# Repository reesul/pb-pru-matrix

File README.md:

# Pocket Beagle Audio Visualizer with LED matrix

Audio visualization is neat so I made a gadget with PocketBeagle for the hell of it! 

[See longer video below](./README.md#video-of-the-thing)

## Project Summary

I made a PCB ("cape" in Beagle terminology) that has an audio jack + electret mic to capture and amplify audio, plus the output cabling for a [LED panel from Adafruit](https://www.adafruit.com/product/2278) (but my extras were cheapo Aliexpress/where-ever and work identically). 

The PocketBeagle (PB) has an AM335x processor for the processing. I capture audio with ADC input in chunks with a sliding window -- sampling rate was set based on processing speed (unoptimized w/ numpy calls) and responsiveness. Audio is processed with FFT -> power log spectrum -> log-frequency power spectrum to make the basis for the image. The image is then an opencv color mapping for each (pseudo-log) frequency bin's power, and send to the PRU via /dev/mem so it can be displayed to the 64x32 LED matrix. The PRU is running a driver to display 8-bit color images, FPS somewhere in 20-30 range.

I chose a pocket beagle, partly because I've worked as an Apps Engineer at TI, partly b I have met the awesome Beagle folks several times, and partly bc I wanted to try running on an SoC with fast IO core + reasonable A-core running Linux. It's worked out well, and the examples were definitely present enough out there to get me started on all aspects of the project. That said, it helps a lot to have worked professionally with such devices to heterogeneous SoCs running a mixture of HLOS/RTOS/No-OS (esp. including Linux) and have a signal processing / embedded systems background. 

## V1 Details

First version of this project is complete as of 2024 EoY. I started sometime in 2023, but didn't put much time into it / slowed down by silly roadblocks. 

This v1 includes:
* Custom cape (PCB that beagle board attaches to) that provides audio input and image output signalling to the matrix panel
   * Revisions needed to reduce analog noise, reduce pinout/external connection, etc.
* PRU code that reads an image from shared memory, and manages output pins for the matrix such that we visualize an 8-bit, 32x64 pixel image. 
   * Framerate is 20-30 FPS and looks about reasonably smooth and responsive, albeit a bit jittery
* Updated device tree overlay for setting ADC configuartion (20kS/s) (see [dtb](./dtb/) files)
   * Data arrives through IIO driver and read with sysfs
   * I noted that bb-overlay repo (origin of these DTS) has an ./install.sh that doesn't work. I had to look in /boot/uEnv.txt to apply the DTBO file (name_overlays)
   * Sampling rate was chosen based on processing speed vs. responsiveness. I wanted 40 kS/s for 20 kHz bandwidth, but this just wasn't feasible. As a result, I have some aliasing in the upper bands that I'll need to resolve later. 
* A bunch of python code to do the audio capture, processing (FFTs and such), and image generation
   * I signal to the PRU by opening /dev/mem to access the whole memory space and write to PRU's shared SRAM. Images too big for rpmsg anyway. 
      * In theory though (thx Jason K. for the tip), I can just alloc a chunk of DDR and access that between both cores -- should be fast enough, but maybe still need double-buffer.
   * Buffer sizes, sampling rates, and processing code are tuned to be snappy -- audio sync tests look visually acceptable (<200ms). Image processing at >30fps, unsure about display
   * I have some filtering to make the frequency bands look smoother in both space (pixels) and time (frames). Could spend lots of time tuning.
   * Add some power switches
   * Check signal levels on home audio system and see if I need to reduce / amplify voltage. Almost certainty the former per Klipsch RP-600m, but must measure at realistic listening level

The fact that this works with Python code and limited optimizations shows that AM335x is still a plenty beefy processor. I'm at ~70% utilization of the 1x A8. That said, I really want a new revision of pocket beagle with a more modern (probably TI) processor, so long as there's a PRU. I'll be keeping an eye out for a new PB iteration ;)  But This would probably also mean a few extra components on the PCB for ADC

The actual code itself for this application is under . There's a main runner script that will turn off the PRU, rebuild firmware, start PRU, apply sysfs settings for ADC capture, and kick off the audio processing + image generation
* My WIP code was put under , and I don't really plan to reorganize this. It's a few piecemeal examples of things like matrix-pru driver, image-generation, sending images to the PRU, audio capture, audio processing 
* Worth noting, my method of sharing images to 

### TODOs in a v2

I got to MVP / PoC, but I know there's more I can do to improve this. Some of those things include (roughly prioritized):

0. Put on beagleprojects with a guide to replicating v1
1. Revise matrix cape to improve signal quality and have easier connections
   - Add low pass filter to have a ~10kHz knee (2-3 taps) to reduce the aliasing I get from 20kS/s samplerate
       * If I can get processing loop fast enough, I can go faster and use 30-40kS/s, but it's diminishing returns on these bands anyway
   - Allow pocket beagle to be powered by 5V from matrix power supply. Have to be careful with USB power though.
       * Also need LDO for matrix
   - Eliminate ground loop that's giving me ugly low frequency noise around 60 Hz
   - Better connector to 5V matrix power supply
2. Measure realizable framerate for single matrix w/ 8-bit color
3. Try extending to a second matrix for longer length
   - Would likely include changing image location for PRU access to be in DDR
   - Will also need to consider realizable framerate relative and bit-depth for ~30 fps
4. Get mounting hardware to affix cape to the matrix panel. Should already have the right footprint for 2.5mm screws 
5. Set explicit FPS target on both display driver and image generation code to make this smoother

And if a PB2 comes out that will work as well, then I'll switch to that. I can burn extra processing on nonsense like:
* beat detection to get a BPM counter/tracker for music
* text display in the top 1/4 of the display
* Shazam or similar API on the backend to identify and print song artist??
   - This might not be free, but would be awesome

But I still want a PRU for the signalling. I suppose newer TI processors have more R5's and similar MCU cores which may be a good alternative, but that seems like more work to port.

##### Video of the thing

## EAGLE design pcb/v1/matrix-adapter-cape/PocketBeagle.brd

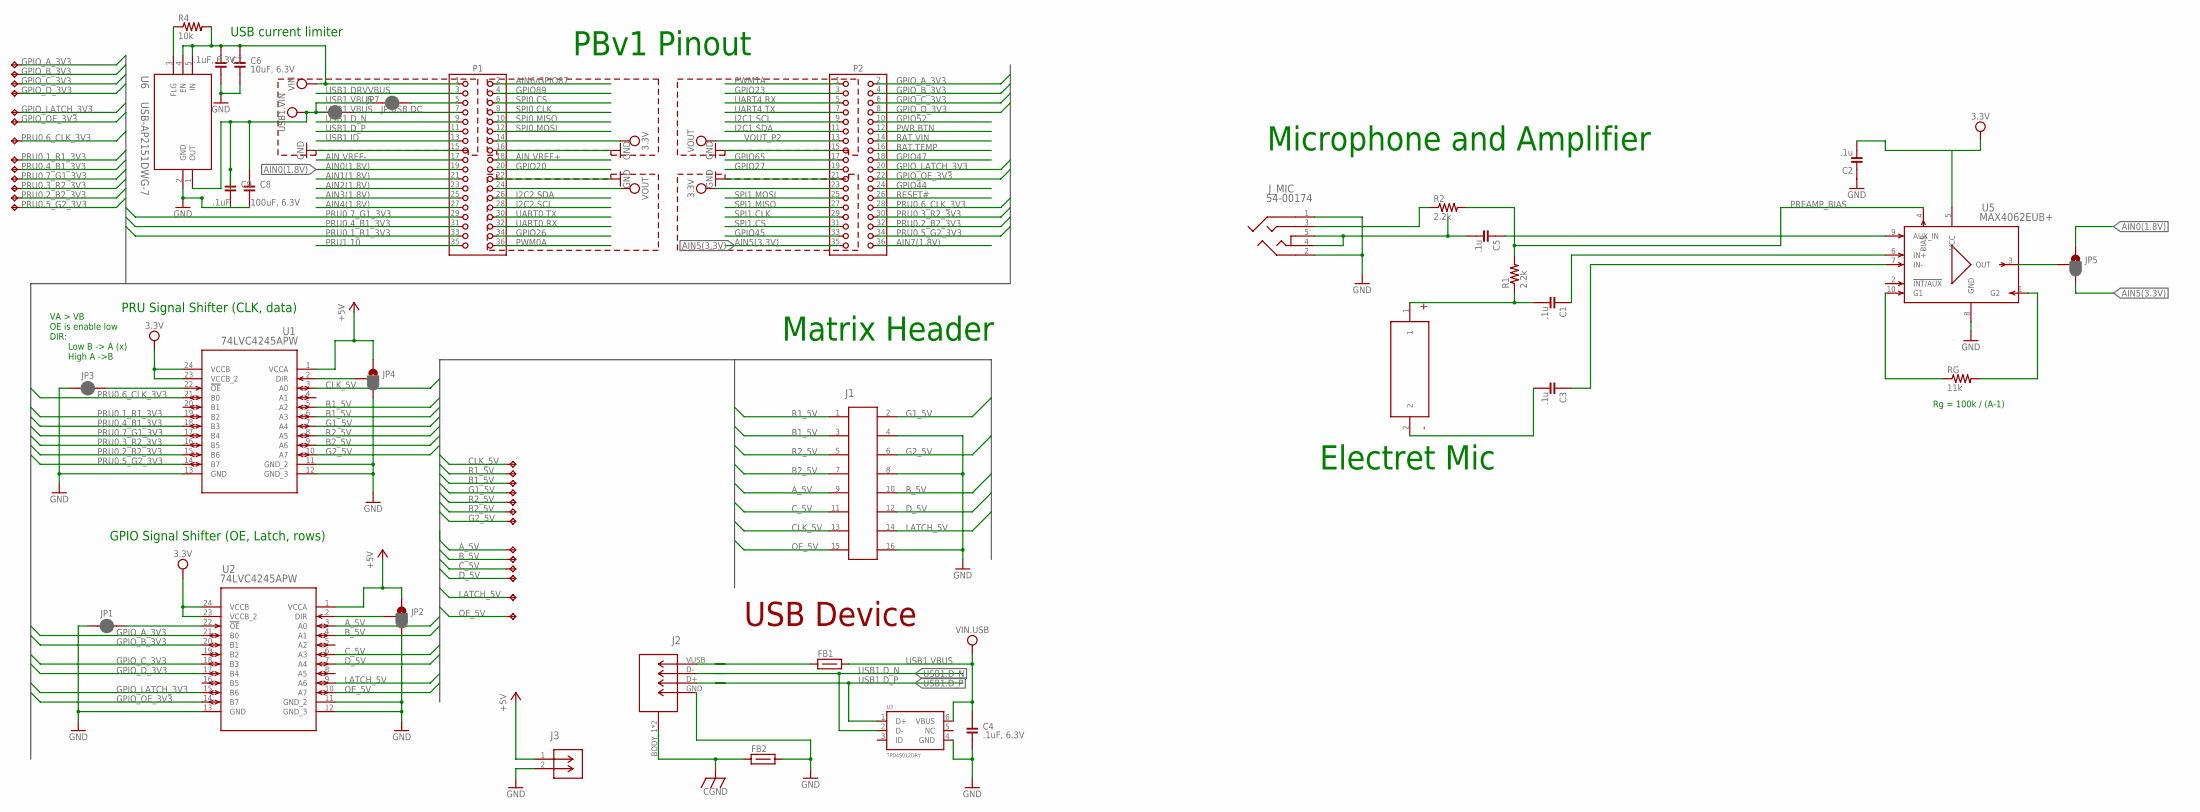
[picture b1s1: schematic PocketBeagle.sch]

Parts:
C1, C2, C3, C5: .1u; C0805
C4, C7: .1uF, 6.3V; C0603
C6: 10uF, 6.3V; C0603
C8: 100uF, 6.3V; C1206
C9: .1uF; C0603
FB1, FB2: FB-(INCH)-0603; 0603; MPN LI0603G121R-10
J1: SBH11-PBPC-D08-ST-BK; CONN16_SBH11-PBPC-D08-ST-BK_SU
J2: USB-61400416021; CONN4_416021_WRE
J3: 1935161; CONN_1935161_PXC
JP1, JP3, JP7, JP.USB.DC: JUMPER-SMT_2_NC_PASTE; SMT-JUMPER_2_LG_NC_PASTE_NO-SILK
JP2, JP4, JP5: JUMPER-SMT_3_1-NC_PASTE_SILK; SMT-JUMPER_3_1-NC_PASTE_SILK
J_MIC: 54-00174; 54-00174_TEN
P1, P2: 2X18-(INCH)-0.1-TH-(35MIL-DIA)-W/O-SILK; TH-2X18-(35MIL-DIA)-W/O-SILK; MPN 61303621121
R1, R2: 2.2k; R0805
R4: 10k; R0805
RG: 11k; R0805
T.A.3, T.A.5, T.B1.3, T.B1.5, T.B2.3, T.B2.5, T.B.3, T.B.5, T.C.3, T.C.5, T.CL.3, T.CL.5, T.D.3, T.D.5, T.G1.3, T.G1.5, T.G2.3, T.G2.5, T.L.3, T.L.5, T.O.3, T.O.5, T.R1.3, T.R1.5, T.R2.3, T.R2.5: TPTP08R; TP08R
U1, U2: 74LVC4245APW; SOT355-1_NEX
U3: TPD4S012DRY; SON-6(TI)-DRY
U4: CMA-4544PF-W; CMA_CUI_9P7X9P7_CUD
U5: MAX4062EUB+; 21-0061L
U6: USB-AP2151DWG-7; SOT25_DIO

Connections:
3V3: C2.2, P1.14, P2.23, U1.23 (VCCB_2), U1.24 (VCCB), U2.23 (VCCB_2), U2.24 (VCCB), U5.5 (VCC)
+5V: J3.1, JP2.1, JP4.1, U1.1 (VCCA), U2.1 (VCCA)
AIN0(1.8V): JP5.1, P1.19
AIN1(1.8V): P1.21
AIN2(1.8V): P1.23
AIN3(1.8V): P1.25
AIN4(1.8V): P1.27
AIN5(3.3V): JP5.3, P2.35
AIN6/GPIO87: P1.2
AIN7(1.8V): P2.36
AIN.VREF+: P1.18
AIN.VREF-: P1.17
A_5V: J1.9, T.A.5.TP, U2.3 (A0)
B1_5V: J1.3, T.B1.5.TP, U1.6 (A3)
B2_5V: J1.7, T.B2.5.TP, U1.9 (A6)
BAT.TEMP: P2.16
BAT.VIN: P2.14
B_5V: J1.10, T.B.5.TP, U2.4 (A1)
CGND: FB2.1, J2.BODY_1 (BODY), J2.BODY_2 (BODY)
CLK_5V: J1.13, T.CL.5.TP, U1.3 (A0)
C_5V: J1.11, T.C.5.TP, U2.6 (A3)
D_5V: J1.12, T.D.5.TP, U2.7 (A4)
G1_5V: J1.2, T.G1.5.TP, U1.7 (A4)
G2_5V: J1.6, T.G2.5.TP, U1.10 (A7)
GND: C2.1, C4.2, C6.2, C7.2, C8.2, C9.2, FB2.2, J1.4, J1.8, J1.16, J2.GND (DGND), J3.2, JP1.2, JP2.3, JP3.2, JP4.3, J_MIC.1, J_MIC.2, P1.15, P1.16, P1.22, P2.15, P2.21, U1.11 (GND_2), U1.12 (GND_3), U1.13 (GND), U2.11 (GND_2), U2.12 (GND_3), U2.13 (GND), U3.4 (GND), U5.8 (GND), U6.2 (GND)
GPIO20: P1.20
GPIO23: P2.3
GPIO26: P1.34
GPIO27: P2.19
GPIO44: P2.24
GPIO45: P2.33
GPIO47: P2.18
GPIO52: P2.10
GPIO65: P2.17
GPIO89: P1.4
GPIO_A_3V3: P2.2, T.A.3.TP, U2.21 (B0)
GPIO_B_3V3: P2.4, T.B.3.TP, U2.20 (B1)
GPIO_C_3V3: P2.6, T.C.3.TP, U2.18 (B3)
GPIO_D_3V3: P2.8, T.D.3.TP, U2.17 (B4)
GPIO_LATCH_3V3: P2.20, T.L.3.TP, U2.15 (B6)
GPIO_OE_3V3: P2.22, T.O.3.TP, U2.14 (B7)
I2C1.SCL: P2.9
I2C1.SDA: P2.11
I2C2.SCL: P1.28
I2C2.SDA: P1.26
JACK_TIP: C5.2, J_MIC.4, J_MIC.5
LATCH_5V: J1.14, T.L.5.TP, U2.9 (A6)
unnamed: JP1.1, U2.22 (!OE)
unnamed: JP2.2, U2.2 (DIR)
unnamed: J_MIC.3, R2.1
unnamed: C3.2, U4.2
unnamed: JP3.1, U1.22 (!OE)
unnamed: C1.2, R1.1, U4.1
unnamed: C1.1, U5.6 (IN+)
unnamed: JP4.2, U1.2 (DIR)
unnamed: C3.1, U5.7 (IN-)
unnamed: RG.2, U5.1 (G2)
unnamed: RG.1, U5.10 (G1)
unnamed: C5.1, U5.9 (AUX_IN)
unnamed: JP5.2, U5.3 (OUT)
unnamed: JP7.1, P1.5
unnamed: JP.USB.DC.1, P1.7
unnamed: R4.1, U6.3 (FLG)
OE_5V: J1.15, T.O.5.TP, U2.10 (A7)
PREAMP_BIAS: R1.2, R2.2, U5.4 (BIAS)
PRU0.1_R1_3V3: P1.33, T.R1.3.TP, U1.19 (B2)
PRU0.2_B2_3V3: P2.32, T.B2.3.TP, U1.15 (B6)
PRU0.3_R2_3V3: P2.30, T.R2.3.TP, U1.16 (B5)
PRU0.4_B1_3V3: P1.31, T.B1.3.TP, U1.18 (B3)
PRU0.5_G2_3V3: P2.34, T.G2.3.TP, U1.14 (B7)
PRU0.6_CLK_3V3: P2.28, T.CL.3.TP, U1.21 (B0)
PRU0.7_G1_3V3: P1.29, T.G1.3.TP, U1.17 (B4)
PRU1.10: P1.35
PWM0A: P1.36
PWM1A: P2.1
PWR.BTN: P2.12
R1_5V: J1.1, T.R1.5.TP, U1.5 (A2)
R2_5V: J1.5, T.R2.5.TP, U1.8 (A5)
RESET#: P2.26
SPI0.CLK: P1.8
SPI0.CS: P1.6
SPI0.MISO: P1.10
SPI0.MOSI: P1.12
SPI1.CLK: P2.29
SPI1.CS: P2.31
SPI1.MISO: P2.27
SPI1.MOSI: P2.25
UART0.RX: P1.32
UART0.TX: P1.30
UART4.RX: P2.5
UART4.TX: P2.7
USB1.DRVVBUS: P1.3
USB1.D_N: J2.D-, P1.9, U3.2 (D-)
USB1.D_P: J2.D+, P1.11, U3.1 (D+)
USB1.ID: P1.13
USB1.VBUS: C4.1, C8.1, C9.1, FB1.2, JP7.2, JP.USB.DC.2, U3.6 (VBUS), U6.1 (OUT)
VBUS.RAW: FB1.1, J2.VUSB (5V)
VIN: C6.1, C7.1, P1.1, R4.2, U6.4 (EN), U6.5 (IN)
VOUT_P1: P1.24
VOUT_P2: P2.13

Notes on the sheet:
USB Device
Matrix Header
PRU Signal Shifter (CLK, data)
GPIO Signal Shifter (OE, Latch, rows)
VA > VB OE is enable low DIR: Low B -> A (x) High A ->B
Microphone and Amplifier
USB current limiter
PBv1 Pinout
Electret Mic
Rg = 100k / (A-1)

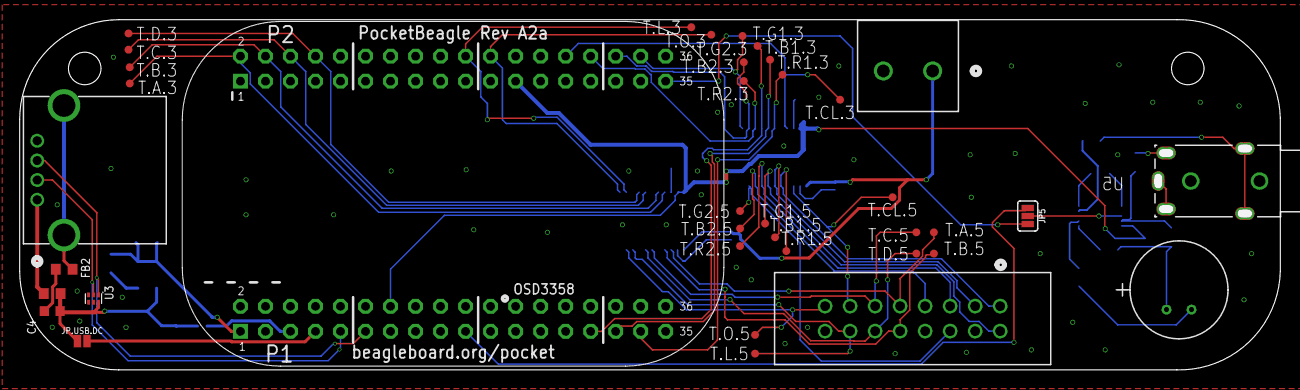
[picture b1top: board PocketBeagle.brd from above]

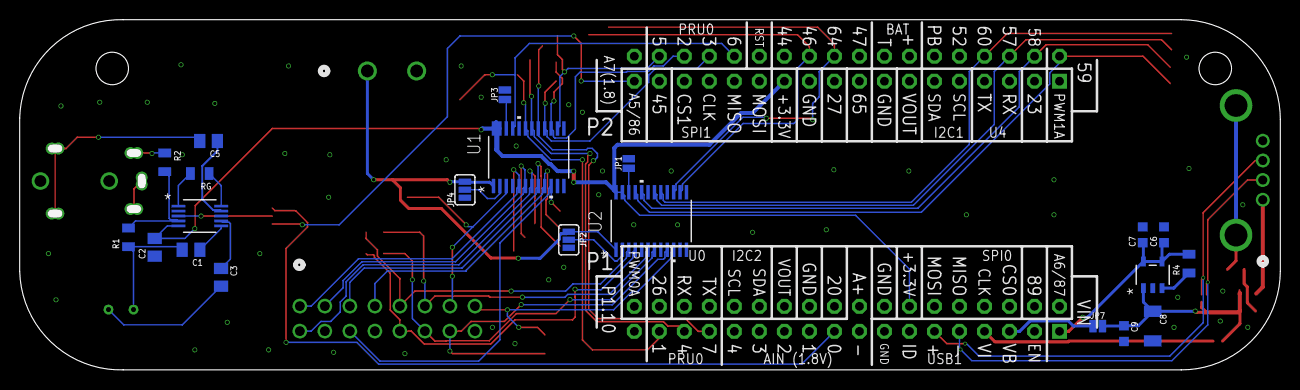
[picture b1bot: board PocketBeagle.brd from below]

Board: 2 copper layers, 127.2 x 34.7 mm, 60 parts (21 on the bottom side), 55 nets.

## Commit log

2024-02-10 Added beagle-sw.drawio
2024-09-02 Add sandbox of demo / test apps
2024-09-02 Add first working version that can display an arbirary image w/ 1-bit RGB color by sending img from Arm/Linux to PRU
2024-09-08 Add v2 matrix-pru source. Includes color-depth. Tested at up to 60 fps and seems smooth enough
2024-09-08 Minor code optimization and cleanup; 8bit color working well and fast enough for 30fps display. Phase 2 effectively complete
2024-09-08 final checkpoint on V2. Debugged a deep memory error preventing a part of one row from copying correctly from shared PRU SRAM to stack
2024-09-08 video of a test pattern scanning across at 30FPS
2024-11-02 Add IIO adc setup script
2024-11-02 experimenting with audio capture; works, but need to modify DTS for higher ADC rate
2024-11-09 add python processing for raw audio to log-binned power spectrum
    seems fast enough for me.. about 32ms to process 100ms chunks of audio
2024-11-09 Add audio test file based on input from desktop DAC (low quality capture)
    song Endlessly by Camelphat, Nadia Ali
2024-12-08 finish basic audio processing to create images, but not validated for accuracy
2024-12-08 First proof of concept!
    lots of TODOs like:
    * make a cooler color-mapping function for viz (cv2 rainbow heatmap?)
    * add smoothing function between windows
2024-12-21 reduce sampling rate to 20kS/s and resolve visual delay to just processing latency
2024-12-28 add a few more features and tuning
2024-12-28 add more efficient image generation and opencv color map
2024-12-28 minor smoothing param changes
2024-12-28 tuning to reduce luminance and visual nosie
2024-12-28 reorganize repo structure
2024-12-28 code reorg and flesh out readme
2025-01-25 code reorg, flesh out readme, add demo video/image
2025-01-25 add PCB files
2025-01-25 Update README.md demo video link
2025-01-25 Update README.md - youtube link to video
2025-01-25 minor readme edti
2025-02-01 tune bufsize
2025-02-01 cleanup and comments
2025-02-23 Commenting and tuning

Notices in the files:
parts and their libraries:
COPYRIGHT: Copyright (C) 2023 Ultra Librarian. All rights reserved.
